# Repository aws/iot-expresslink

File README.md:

## AWS IoT ExpressLink

Watch [this overview presentation](https://www.youtube.com/watch?v=6K9knXZpC8A) to get a better understanding of what AWS IoT ExpressLink provides.

This repository contains examples for integrating an AWS IoT ExpressLink module into an application.  These examples are intended to demonstrate how to perform the common operations for an IoT device.

The AWS IoT ExpressLink AT command specification can be found in the [Programmer's Manual](https://docs.aws.amazon.com/iot-expresslink).

Information about AWS IoT ExpressLink and partner's hardware modules can be found at AWS Partner Network's Device Catalog from the [main page](https://aws.amazon.com/iot-expresslink). Module datasheet, Getting Started Guide, and Product Information are also included in the device catalog.

## Documentation

* [AWS IoT ExpressLink Programmer's Guide](https://docs.aws.amazon.com/iot-expresslink/latest/programmersguide/elpg.html)
* [AWS IoT ExpressLink Getting Started Guide](https://docs.aws.amazon.com/iot-expresslink/latest/gettingstartedguide/elgsg.html)
* [AWS IoT ExpressLink Onboarding-by-Claim Customer/OEM Guide](https://docs.aws.amazon.com/iot-expresslink/latest/oemonboardingguide/oemog.html)

## Prototyping SDK libraries
### C libraries
ExpressLink drivers and examples written in C for different MCU platforms.
#### STM32
CMSIS pack for ExpressLink driver and examples, integrated with STM32CubeMX, the native configuration and code generation tool from STMicroelectronics.
The combination enables developers to quickly and easily create applications that connect to AWS IoT Core using ExpressLink modules with various STM32 MCUs.
https://github.com/stm32-hotspot/I-CUBE-ExpressLink

### Python, CircuitPython, MicroPython

For Python, including CircuitPython, MicroPython, and standard Python on Linux, macOS, and Windows:
https://github.com/awslabs/aws-iot-expresslink-library-python

### Arduino

For Arduino and all all microcontrollers that support the Arduino platform:
https://github.com/awslabs/aws-iot-expresslink-library-arduino

## Web Resources

* [AWS IoT ExpressLink product page](https://aws.amazon.com/iot-expresslink/?nc=sn&loc=1)
* [AWS Partner Device Catalog for qualified AWS IoT ExpressLink hardware](https://devices.amazonaws.com/search?page=1&sv=iotxplnk)

## User Guides

The user guides can be found under the folder [cloud_templates/user_guides](cloud_templates/user_guides).

### Espressif

[Getting Started Guide for Espressif's AWS IoT ExpressLink Evaluation Kit on GitHub](https://github.com/espressif/esp-aws-expresslink-eval)

### Realtek

[Realtek's Ameba Z2 AWS IoT ExpressLink Evaluation Kit on GitHub](https://github.com/ambiot/ambz2_aws_iot_expresslink_eval)

### u-blox

[u-blox' USB-NORA-W256AWS AWS IoT ExpressLink Multiradio development kit](https://www.u-blox.com/en/product/usb-nora-w2?legacy=Current#Documentation-&-resources)

[u-blox' SARA-R510AWS module LTE-M AWS IoT ExpressLink module](https://www.u-blox.com/en/product/sara-r510aws-module?legacy=Current#Documentation-&-resources)

### Telit

[Telit's Bravo AWS IoT ExpressLink development kit on GitHub](https://github.com/telit/bravo-aws-expresslink)

## Hands-On Workshops and Resources

The **AWS IoT ExpressLink Demo Badge Workshop** is available at https://catalog.workshops.aws/aws-iot-expresslink-demo-badge/. This workshop ran as *IOT207-R* on November 28, and as *IOT207-R1* on December 2, at AWS re:Invent 2022.

The *Advanced Lab Modules* of the AWS re:Invent 2022 workshop used a Python library to quickly prototype an integration with AWS IoT ExpressLink using Python. The evolution of this early library is now available in this GitHub repository:
[awslabs/aws-iot-expresslink-library-python](https://github.com/awslabs/aws-iot-expresslink-library-python)

## Hardware Designs

The **AWS IoT ExpressLink Demo Badge hardware design**, with full schematics and PCB layout files, is available under the [hardware designs folder](./hardware-designs/).

## Blog Posts and Application Notes

* [Introducing AWS IoT ExpressLink, making it faster and easier to develop secure IoT devices](https://aws.amazon.com/blogs/iot/introducing-aws-iot-expresslink-making-it-faster-and-easier-to-develop-secure-iot-devices/) published 2021-11-30.
* [AWS IoT ExpressLink is now generally available](https://aws.amazon.com/about-aws/whats-new/2022/06/aws-iot-expresslink-generally-available/) published 2022-06-22.

## Twitch series: All Things AWS IoT ExpressLink

* Live stream on AWS Twitch channel - https://twitch.tv/aws
* Aired Tuesdays, 8am - 9am Pacific
* 15 episodes from March 15 - June 21, 2022
* Hosted by Dan Gross

 Episode    | Date       | Link                                       | Guest(s)                         | Partner  |
 ---------- | ---------- | ------------------------------------------ | -------------------------------- | -------- |
 Episode 1  | 2022-03-15 | https://www.twitch.tv/aws/video/1486749698 | Lucio, Michael                   |          |
 Episode 2  | 2022-03-22 | https://www.twitch.tv/aws/video/1486743174 | Lucio                            |          |
 Episdoe 3  | 2022-03-29 | https://www.twitch.tv/aws/video/1308163094 | Lucio, Magnus, Harald            | u-blox   |
 Episode 4  | 2022-04-05 | https://www.twitch.tv/aws/video/1314933253 | Lucio, Cobus, Joe                |          |
 Episode 5  | 2022-04-12 | https://www.twitch.tv/aws/video/1499049648 | Lucio, Harald, Magnus, Leo       | u-blox   |
 Episode 6  | 2022-04-19 | https://www.twitch.tv/aws/video/1507258985 | Cobus, Richard, Michael          |          |
 Episode 7  | 2022-04-26 | https://www.twitch.tv/aws/video/1507261412 | Lucio, Anton, Amey               | Espressif|
 Episode 8  | 2022-05-03 | https://www.twitch.tv/aws/video/1507263672 | Lucio, Joe                       |          |
 Episode 9  | 2022-05-10 | https://www.twitch.tv/aws/video/1507266090 | Lucio, Amey, Dhaval              | Espressif|
 Episode 10 | 2022-05-17 | https://www.twitch.tv/aws/video/1507267356 | Lucio, Yasser                    |          |
 Episode 11 | 2022-05-24 | https://www.twitch.tv/aws/video/1532014170 | Lucio, Amit, Prejith             | Infineon |
 Episode 12 | 2022-05-31 | https://www.twitch.tv/aws/video/1532015120 | Lucio, Joe                       |          |
 Episode 13 | 2022-06-07 | https://www.twitch.tv/aws/video/1532015794 | Lucio, Amit                      | Infineon |
 Episode 14 | 2022-06-14 | https://www.twitch.tv/aws/video/1532016601 | Lucio, Mike                      |          |
 Episode 15 | 2022-06-21 | https://www.twitch.tv/aws/video/1532017442 | Lucio, Steve, Magnus, Amey, Dave | All      |
 Episode 16 | 2022-11-22 | https://www.twitch.tv/aws/video/1690204748 | Lucio, Jefferson, Elleson, Shimis| Realtek |

## YouTube Videos

* [Playlist: Building a Weather Station](https://www.youtube.com/watch?v=hGBIzlp68bU&list=PLhr1KZpdzukdy_S7NpE9kkC75SXUCMYdO)
* [Espressif's AWS IoT ExpressLink Solution](https://www.youtube.com/watch?v=NSGCVH0OU7w)
* [u-blox AWS IoT ExpressLink](https://www.youtube.com/watch?v=4GiBnT0I0HE)
* [AWS IoT ExpressLink and the u-blox NORA-W2](https://www.youtube.com/watch?v=PvyzQwVgCCw)
* [Product Showcase: AWS IoT ExpressLink SARA-R5 Starter Kit](https://www.youtube.com/watch?v=nJNYUP0413c)
* [AIROC™ Cloud Connectivity Manager module & AWS IoT ExpressLink](https://www.youtube.com/watch?v=LEGDyNXPYfc)
* [Innovation Coffee with AWS IoT ExpressLink](https://www.youtube.com/watch?v=K0saFj-6s6c)
* [Connecting AWS IoT ExpressLink to an MQTT Broker running on AWS IoT Greengrass](https://www.youtube.com/watch?v=ii59MiFVIDI)

## Security

See [CONTRIBUTING](CONTRIBUTING.md#security-issue-notifications) for more information.

## License

The resources in this repository are licensed under the MIT-0 License. See the LICENSE file.

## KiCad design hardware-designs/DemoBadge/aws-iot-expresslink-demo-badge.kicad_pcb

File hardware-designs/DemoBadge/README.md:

# AWS IoT ExpressLink Demo Badge

This device was designed and created for the [AWS IoT ExpressLink Demo Badge Workshop](https://catalog.workshops.aws/aws-iot-expresslink-demo-badge/), which was run at re:Invent 2022.

The Demo Badge features an RP2040 microcontroller, an Espressif ESP32-C3-MINI-1-A AWS IoT ExpressLink module, various sensors, buttons, RGB LEDs, and a color display.

You can find more information about the device itself, and its components, as part of the [workshop appendix](https://catalog.workshops.aws/aws-iot-expresslink-demo-badge/en-US/7-appendix).

## Schematic

The schematic for the Demo Badge is available as KiCAD 6 project. You can access a [PDF version of the single-sheet schematic here](./snapshot/Schematic/aws-iot-expresslink-demo-badge-schematic.pdf).

## PCB Layout

The PCB layout for the Demo Badge is available as KiCAD 6 project, including all footprints (publicly available ones, and custom ones).

You can access the [production Gerber files here](./snapshot/Manufacturers/JLCPCB/).

## Re-generate Gerbers and other files

If you made any changes to the PCB layout, you have to re-generate the Gerbers files before sending them to your PCB manufacturer. You can use [KiBot](https://github.com/INTI-CMNB/KiBot) to generate Gerbers and other files in a repeatable way using the `kibot.yaml` configuration file.

You can follow the KiBot installation guide, or use a Docker container:

```bash
docker run --rm -v "$PWD":/kicad -w /kicad setsoft/kicad_auto:ki6 kibot -c kibot.yaml
```

All KiBot-generated files are available under `Generated/`.

## License

This hardware design is licensed under the MIT-0 License. Imported footprints and 3D models might contain different licenses.

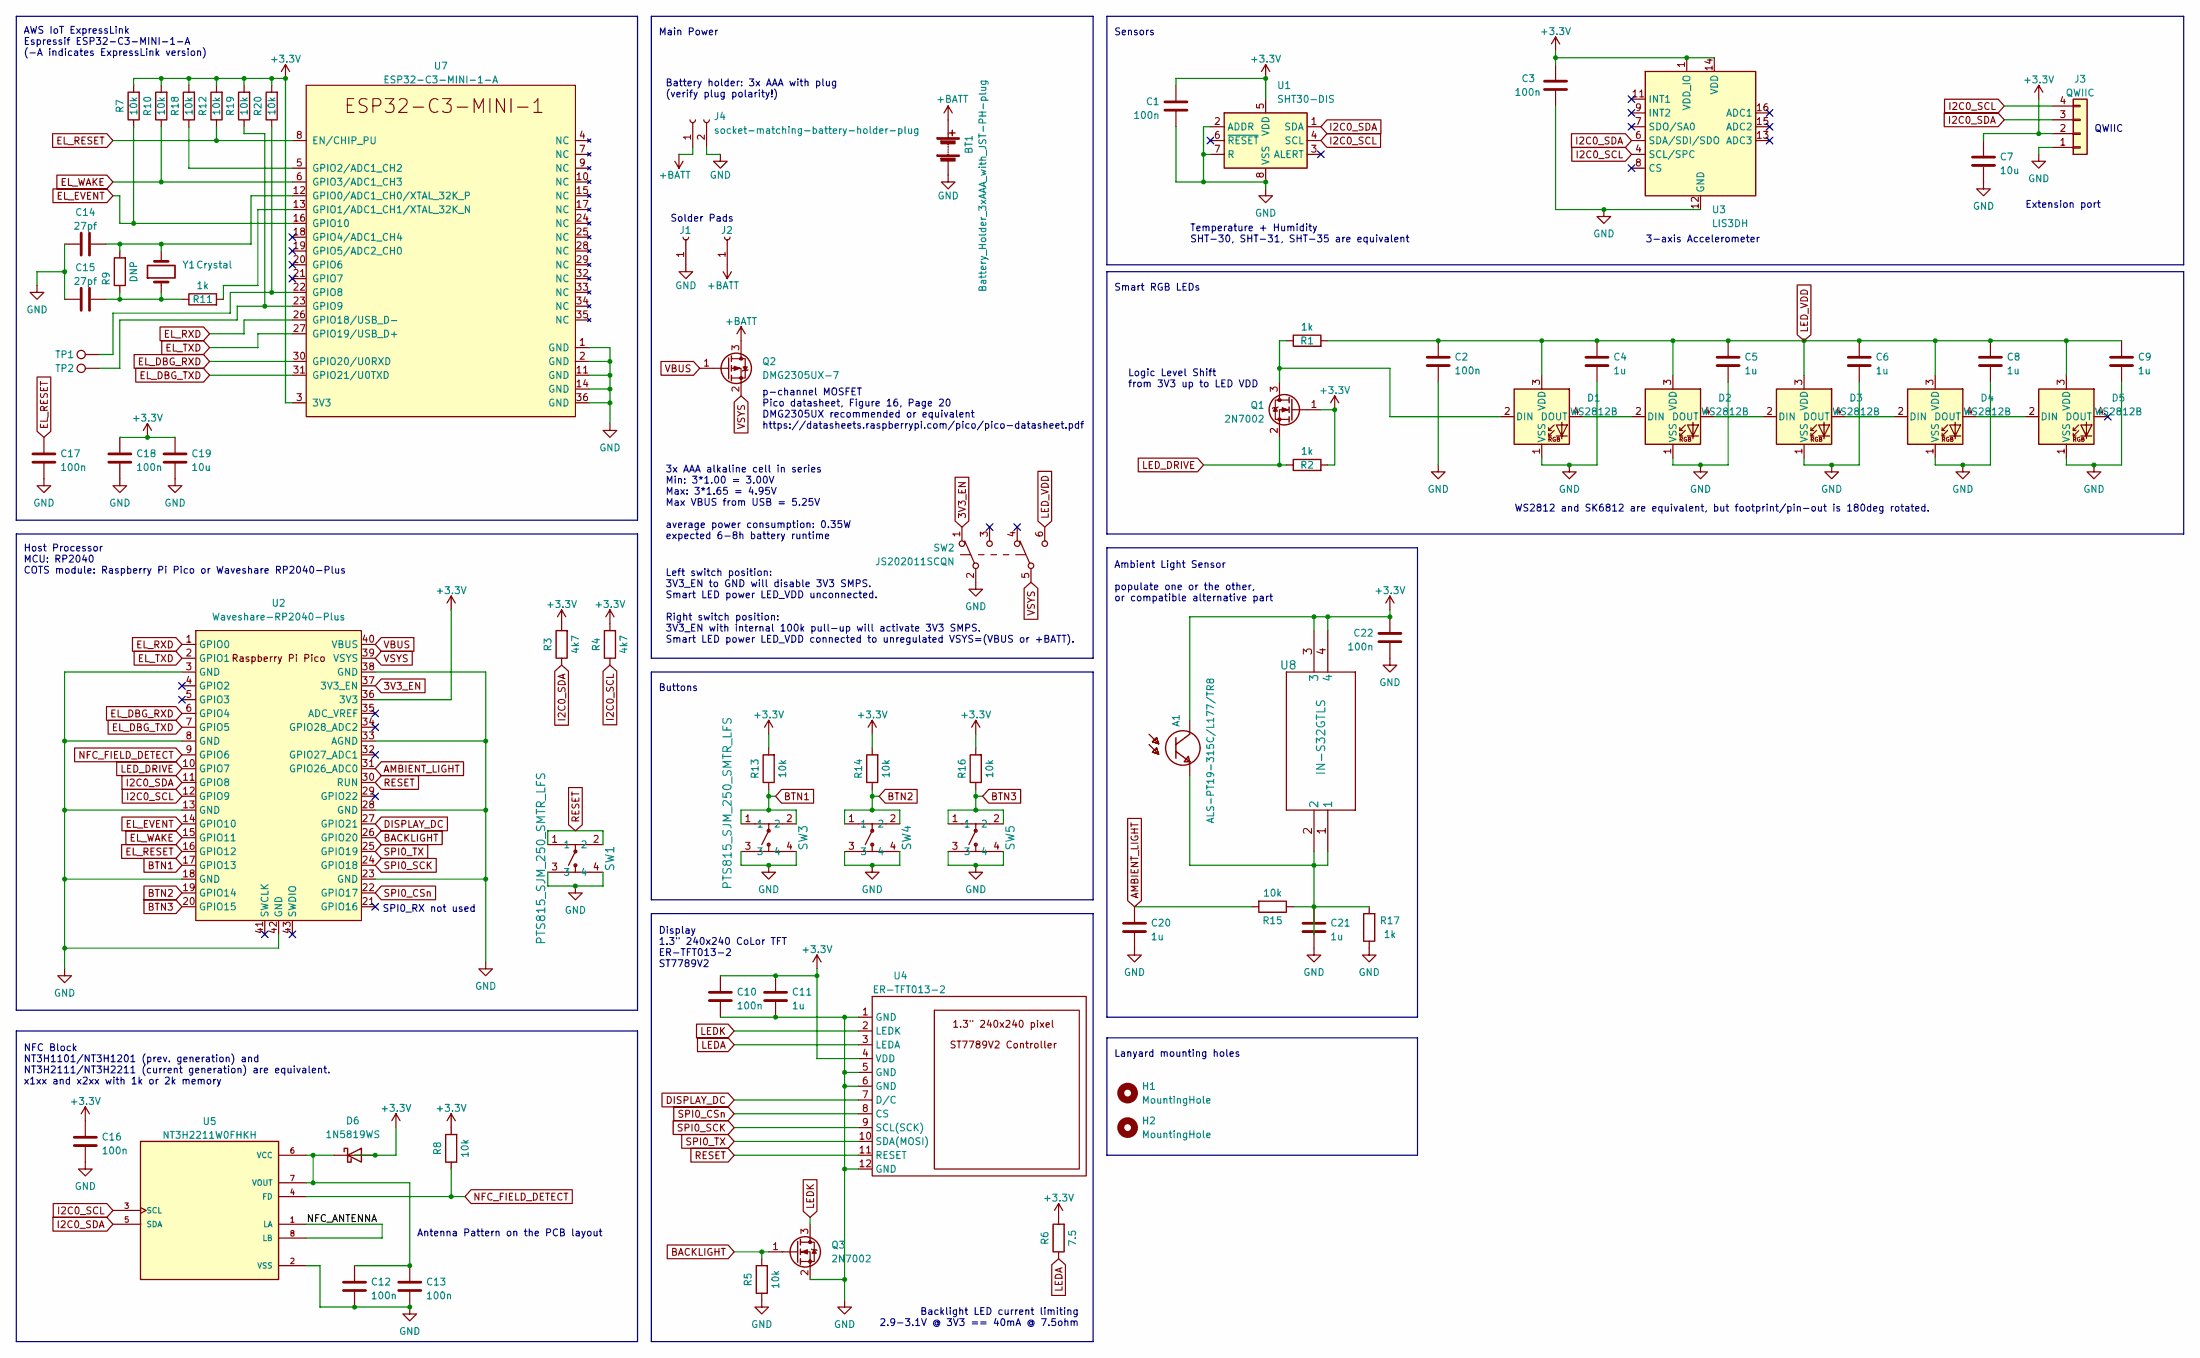
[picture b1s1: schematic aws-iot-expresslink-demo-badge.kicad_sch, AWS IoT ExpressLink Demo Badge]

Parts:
A1: ALS-PT19-315C/L177/TR8; XDCR_ALS-PT19-315C_L177_TR8; LCSC# C146233
BT1: Battery_Holder_3xAAA_with_JST-PH-plug
C1, C2, C3, C10, C12, C13, C16, C17, C18, C22: 100n; C_0603_1608Metric; LCSC# C14663
C4, C5, C6, C8, C9, C11, C20, C21: 1u; C_0603_1608Metric; LCSC# C15849
C7, C19: 10u; C_0603_1608Metric; LCSC# C19702
C14, C15: 27pf; C_0603_1608Metric; LCSC# C107045
D1, D2, D3, D4, D5: WS2812B; SK6812-multi; LCSC# C2874885
D6: 1N5819WS; D_SOD-323; LCSC# C191023
H1, H2: MountingHole; lanyard-cutout
J1: BATT_NEG; TestPoint_Pad_D2.0mm
J2: BATT_POS; TestPoint_Pad_D2.0mm
J3: QWIIC; JST_SH_SM04B-SRSS-TB_1x04-1MP_P1.00mm_Horizontal; LCSC# C145956
J4: socket-matching-battery-holder-plug; JST_PH_S2B-PH-K_1x02_P2.00mm_Horizontal; LCSC# C173752
Q1, Q3: 2N7002; SOT-23; LCSC# C8545
Q2: DMG2305UX-7; SOT-23; LCSC# C150470
R1, R2, R11, R17: 1k; R_0603_1608Metric; LCSC# C21190
R3, R4: 4k7; R_0603_1608Metric; LCSC# C105428
R5, R7, R8, R10, R12, R13, R14, R15, R16, R18, R19, R20: 10k; R_0603_1608Metric; LCSC# C25804
R6: 7.5; R_0603_1608Metric; LCSC# C365480
R9: DNP; R_0603_1608Metric
SW1, SW3, SW4, SW5: PTS815_SJM_250_SMTR_LFS; PTS815 SJM 250 SMTR LFS; LCSC# C2689510
SW2: JS202011SCQN; LCSC# C221666
TP1, TP2: TestPoint; TestPoint_Pad_D1.0mm
U1: SHT30-DIS; Sensirion_DFN-8-1EP_2.5x2.5mm_P0.5mm_EP1.1x1.7mm; LCSC# C77361
U2: Waveshare-RP2040-Plus; LCSC# C5159530
U3: LIS3DH; LGA-16_3x3mm_P0.5mm_LayoutBorder3x5y; LCSC# C15134
U4: ER-TFT013-2
U5: NT3H2211W0FHKH; IC_NT3H2211W0FHKH; LCSC# C2905792
U7: ESP32-C3-MINI-1-A; ESP32-C3-MINI-1; LCSC# C5224444
U8: IN-S32GTLS
Y1: Crystal; Crystal_SMD_3215-2Pin_3.2x1.5mm; LCSC# C32346

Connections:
3V3_EN: SW2.1 (A), U2.37 (3V3_EN)
+3.3V: A1.1, C1.2, C3.2, C7.2, C10.2, C11.2, C16.2, C18.2, C19.2, C22.2, D6.2 (A), J3.2, Q1.1 (G), R2.2, R3.2, R4.2, R6.2, R7.2, R8.2, R10.2, R12.2, R13.2, R14.2, R16.2, R18.2, R19.2, R20.2, U1.5 (VDD), U2.36 (3V3), U3.1 (VDD_IO), U3.14 (VDD), U4.4 (VDD), U7.3 (3V3), U8.3, U8.4
+BATT: BT1.1 (+), J2.1, J4.1, Q2.3 (D)
/NFC_ANTENNA: U5.1 (LA), U5.8 (LB)
AMBIENT_LIGHT: C20.2, R15.2, U2.31 (GPIO26_ADC0)
BACKLIGHT: Q3.1 (G), R5.2, U2.26 (GPIO20)
BTN1: R13.1, SW3.1, SW3.2, U2.17 (GPIO13)
BTN2: R14.1, SW4.1, SW4.2, U2.19 (GPIO14)
BTN3: R16.1, SW5.1, SW5.2, U2.20 (GPIO15)
DISPLAY_DC: U2.27 (GPIO21), U4.7 (D/C)
EL_DBG_RXD: U2.6 (GPIO4), U7.30 (GPIO20/U0RXD)
EL_DBG_TXD: U2.7 (GPIO5), U7.31 (GPIO21/U0TXD)
EL_EVENT: R7.1, U2.14 (GPIO10), U7.16 (GPIO10)
EL_RESET: C17.1, R12.1, U2.16 (GPIO12), U7.8 (EN/CHIP_PU)
EL_RXD: U2.1 (GPIO0), U7.26 (GPIO18/USB_D-)
EL_TXD: U2.2 (GPIO1), U7.27 (GPIO19/USB_D+)
EL_WAKE: R10.1, U2.15 (GPIO11), U7.6 (GPIO3/ADC1_CH3)
GND: BT1.2 (-), C1.1, C2.1, C3.1, C4.1, C5.1, C6.1, C7.1, C8.1, C9.1, C10.1, C11.1, C12.1, C13.1, C14.1, C15.1, C16.1, C17.2, C18.1, C19.1, C20.1, C21.1, C22.1, D1.1 (VSS), D2.1 (VSS), D3.1 (VSS), D4.1 (VSS), D5.1 (VSS), J1.1, J3.1, J4.2, Q3.2 (S), R5.1, R17.1, SW1.3, SW1.4, SW2.2 (B), SW3.3, SW3.4, SW4.3, SW4.4, SW5.3, SW5.4, U1.2 (ADDR), U1.7 (R), U1.8 (VSS), U1.9 (VSS), U2.3 (GND), U2.8 (GND), U2.13 (GND), U2.18 (GND), U2.23 (GND), U2.28 (GND), U2.33 (AGND), U2.38 (GND), U2.42 (GND), U3.5 (GND), U3.10 (GND), U3.12 (GND), U4.1 (GND), U4.5 (GND), U4.6 (GND), U4.12 (GND), U5.2 (VSS), U7.1 (GND), U7.2 (GND), U7.11 (GND), U7.14 (GND), U7.36 (GND)
I2C0_SCL: J3.4, R4.1, U1.4 (SCL), U2.12 (GPIO9), U3.4 (SCL/SPC), U5.3 (SCL)
I2C0_SDA: J3.3, R3.1, U1.1 (SDA), U2.11 (GPIO8), U3.6 (SDA/SDI/SDO), U5.5 (SDA)
LEDA: R6.1, U4.3 (LEDA)
LEDK: Q3.3 (D), U4.2 (LEDK)
LED_DRIVE: Q1.2 (S), R2.1, U2.10 (GPIO7)
LED_VDD: C2.2, C4.2, C5.2, C6.2, C8.2, C9.2, D1.3 (VDD), D2.3 (VDD), D3.3 (VDD), D4.3 (VDD), D5.3 (VDD), R1.2, SW2.6 (C)
NFC_FIELD_DETECT: R8.1, U2.9 (GPIO6), U5.4 (FD)
unnamed: A1.2, C21.2, R15.1, R17.2, U8.1, U8.2
unnamed: C12.2, C13.2, D6.1 (K), U5.6 (VCC), U5.7 (VOUT)
unnamed: C14.2, R9.2, U7.12 (GPIO0/ADC1_CH0/XTAL_32K_P), Y1.2
unnamed: C15.2, R9.1, R11.1, Y1.1
unnamed: D1.2 (DIN), Q1.3 (D), R1.1
unnamed: D1.4 (DOUT), D2.2 (DIN)
unnamed: D2.4 (DOUT), D3.2 (DIN)
unnamed: D3.4 (DOUT), D4.2 (DIN)
unnamed: D4.4 (DOUT), D5.2 (DIN)
unnamed: R11.2, U7.13 (GPIO1/ADC1_CH1/XTAL_32K_N)
unnamed: R18.1, U7.5 (GPIO2/ADC1_CH2)
unnamed: R19.1, TP2.1, U7.23 (GPIO9)
unnamed: R20.1, TP1.1, U7.22 (GPIO8)
RESET: SW1.1, SW1.2, U2.30 (RUN), U4.11 (RESET)
SPI0_CSn: U2.22 (GPIO17), U4.8 (CS)
SPI0_SCK: U2.24 (GPIO18), U4.9 (SCL(SCK))
SPI0_TX: U2.25 (GPIO19), U4.10 (SDA(MOSI))
VBUS: Q2.1 (G), U2.40 (VBUS)
VSYS: Q2.2 (S), SW2.5 (B), U2.39 (VSYS)

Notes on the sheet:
Solder Pads
Main Power
Sensors
Host Processor MCU: RP2040 COTS module: Raspberry Pi Pico or Waveshare RP2040-Plus
AWS IoT ExpressLink Espressif ESP32-C3-MINI-1-A (-A indicates ExpressLink version)
Left switch position: 3V3_EN to GND will disable 3V3 SMPS. Smart LED power LED_VDD unconnected. Right switch position: 3V3_EN with internal 100k pull-up will activate 3V3 SMPS. Smart LED power LED_VDD connected to unregulated VSYS=(VBUS or +BATT).
NFC Block NT3H1101/NT3H1201 (prev. generation) and NT3H2111/NT3H2211 (current generation) are equivalent. x1xx and x2xx with 1k or 2k memory
SPI0_RX not used
3-axis Accelerometer
Smart RGB LEDs
Battery holder: 3x AAA with plug (verify plug polarity!)
Display 1.3" 240x240 CoLor TFT ER-TFT013-2 ST7789V2
Logic Level Shift from 3V3 up to LED VDD
3x AAA alkaline cell in series Min: 3*1.00 = 3.00V Max: 3*1.65 = 4.95V Max VBUS from USB = 5.25V average power consumption: 0.35W expected 6-8h battery runtime
p-channel MOSFET Pico datasheet, Figure 16, Page 20 DMG2305UX recommended or equivalent https://datasheets.raspberrypi.com/pico/pico-datasheet.pdf
Temperature + Humidity SHT-30, SHT-31, SHT-35 are equivalent
QWIIC
Lanyard mounting holes
Extension port
Antenna Pattern on the PCB layout
Ambient Light Sensor populate one or the other, or compatible alternative part
WS2812 and SK6812 are equivalent, but footprint/pin-out is 180deg rotated.
Buttons
Backlight LED current limiting 2.9-3.1V @ 3V3 == 40mA @ 7.5ohm

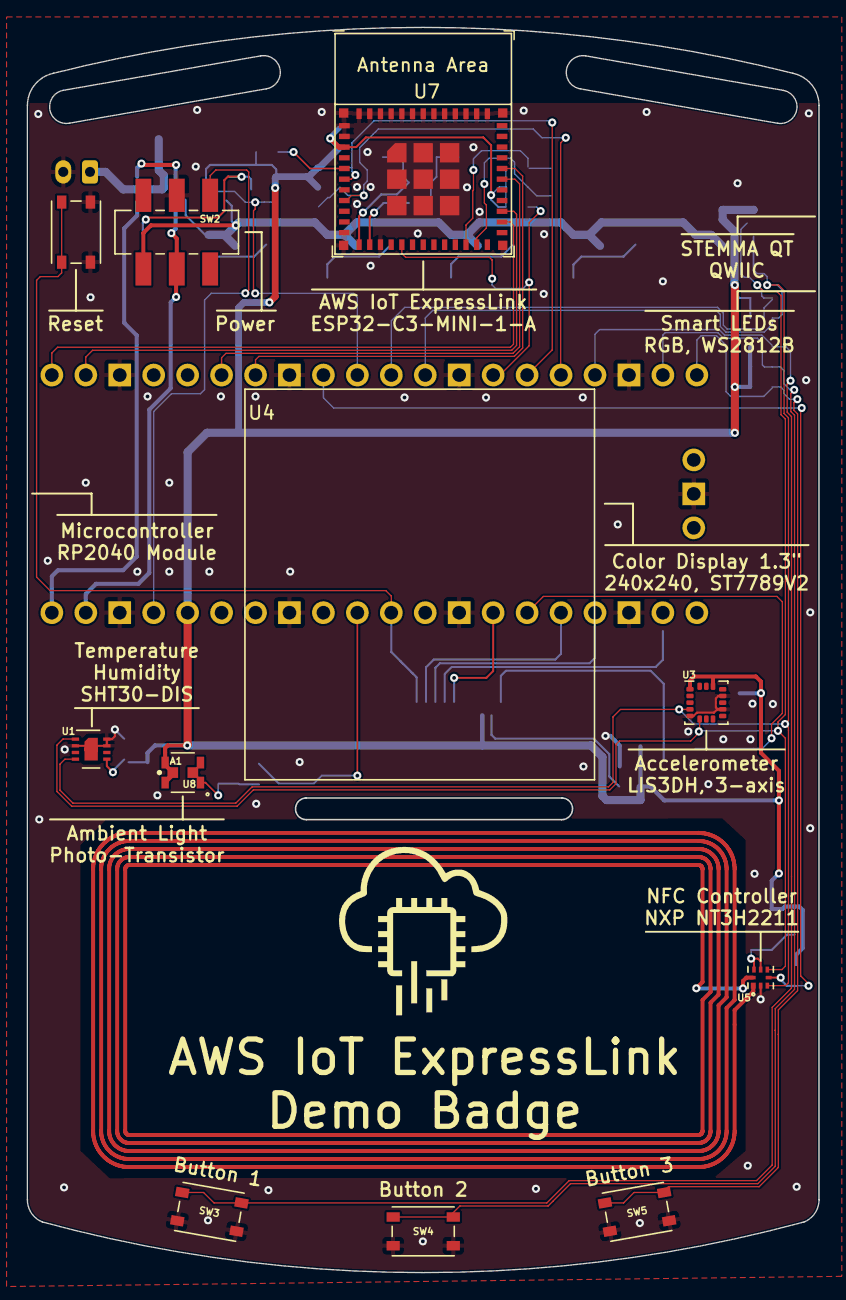
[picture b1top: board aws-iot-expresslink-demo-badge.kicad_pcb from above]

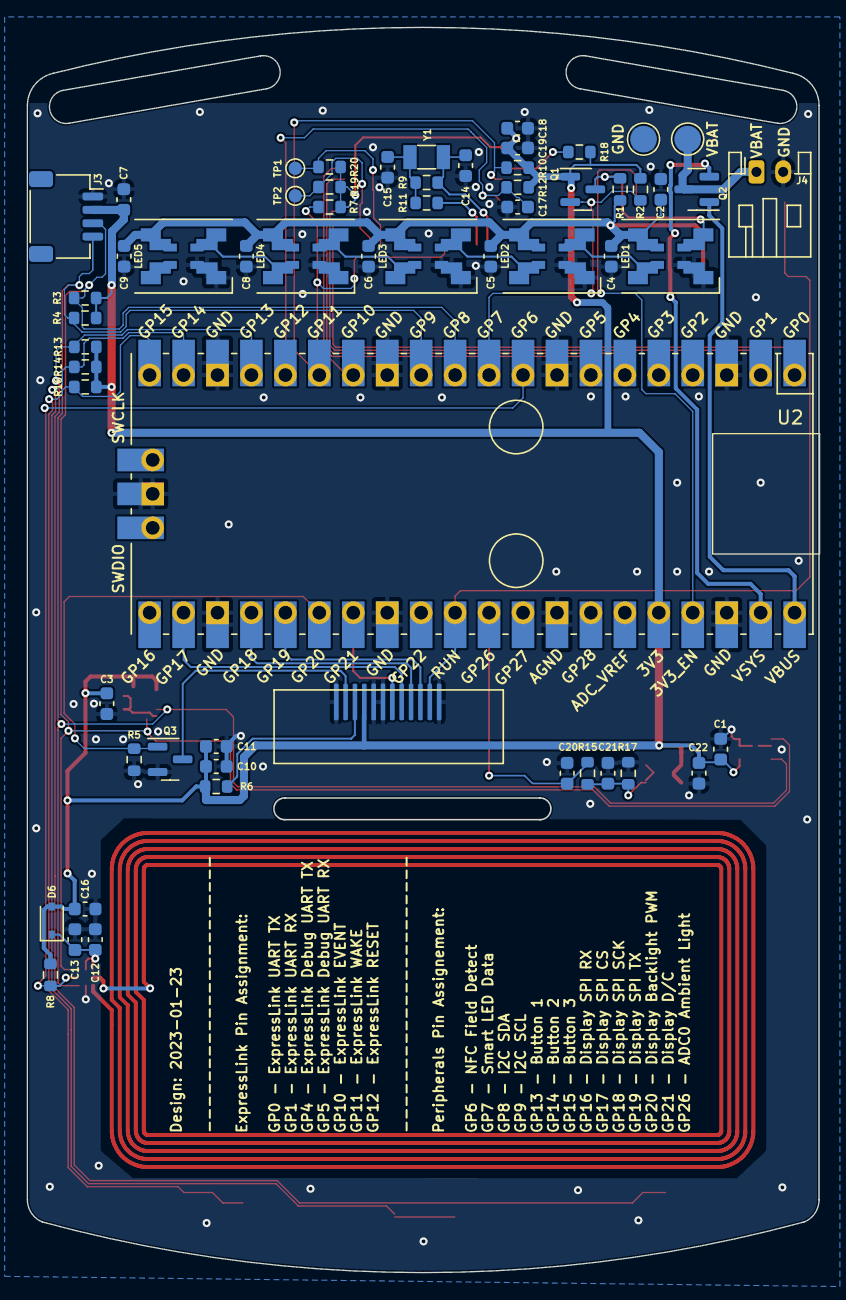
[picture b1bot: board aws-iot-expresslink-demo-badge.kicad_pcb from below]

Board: 2 copper layers, 59.2 x 93.2 mm, 73 parts (59 on the bottom side), 44 nets.

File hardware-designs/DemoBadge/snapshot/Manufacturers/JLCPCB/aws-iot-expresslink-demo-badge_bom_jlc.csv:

"Comment","Designator","Footprint","LCSC Part #"
"ALS-PT19-315C/L177/TR8","A1","XDCR_ALS-PT19-315C_L177_TR8","C146233"
"27pf","C14,C15","C_0603_1608Metric","C107045"
"100n","C1,C2,C3,C10,C12,C13,C16,C17,C18,C22","C_0603_1608Metric","C14663"
"1u","C4,C5,C6,C8,C9,C11,C20,C21","C_0603_1608Metric","C15849"
"10u","C7,C19","C_0603_1608Metric","C19702"
"1N5819WS","D6","D_SOD-323","C191023"
"WS2812B","D1,D2,D3,D4,D5","SK6812-multi","C2874885"
"QWIIC","J3","JST_SH_SM04B-SRSS-TB_1x04-1MP_P1.00mm_Horizontal","C145956"
"socket-matching-battery-holder-plug","J4","JST_PH_S2B-PH-K_1x02_P2.00mm_Horizontal","C173752"
"2N7002","Q1,Q3","SOT-23","C8545"
"DMG2305UX-7","Q2","SOT-23","C150470"
"7.5","R6","R_0603_1608Metric","C365480"
"1k","R1,R2,R11,R17","R_0603_1608Metric","C21190"
"4k7","R3,R4","R_0603_1608Metric","C105428"
"10k","R5,R7,R8,R10,R12,R13,R14,R15,R16,R18,R19,R20","R_0603_1608Metric","C25804"
"JS202011SCQN","SW2","JS202011SCQN","C221666"
"PTS815_SJM_250_SMTR_LFS","SW1,SW3,SW4,SW5","PTS815 SJM 250 SMTR LFS","C2689510"
"ESP32-C3-MINI-1-A","U7","ESP32-C3-MINI-1","C5224444"
"LIS3DH","U3","LGA-16_3x3mm_P0.5mm_LayoutBorder3x5y","C15134"
"NT3H2211W0FHKH","U5","IC_NT3H2211W0FHKH","C2905792"
"SHT30-DIS","U1","Sensirion_DFN-8-1EP_2.5x2.5mm_P0.5mm_EP1.1x1.7mm","C77361"
"Waveshare-RP2040-Plus","U2","Waveshare-RP2040-Plus","C5159530"
"Crystal","Y1","Crystal_SMD_3215-2Pin_3.2x1.5mm","C32346"

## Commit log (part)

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2021-11-19 Initial checkin of first projects
2021-11-19 simplified code
2021-11-30 Create CODEOWNERS
2021-11-30 Add PULL_REQUEST_TEMPLATE
2021-12-23 Update README.md
    Add link to RedBoard Turbo Fun set up instruction.
2022-04-01 removed TopicRoot set... this should be pre-provisioned
2022-04-01 Added grafana demo to arduino examples
2022-04-04 Tweaks to the data report
2022-04-29 First working version of the Cellular ExpressLink WeatherStation
2022-04-29 Removed the topicroot from the prefix of the data topic
2022-05-03 Updated the reconnection strategy
2022-05-09 Adding Arduino Uno example for weather station project
2022-08-16 Added the AWS CDK code for the patterns - first version
2022-08-24 Deletes the massive directory
2022-08-24 Added Timestream pattern material
2022-08-24 Updated the top-level README
2022-08-24 Added the demo main.cpp file and its instructions
2022-08-24 Added the IoT Analytics pattern material
2022-08-25 Seperated Timestream branch from main
2022-08-25 Added the common directory - common files and functions between all the patterns
2022-08-25 Added the common directory - common files and functions for all the patterns
2022-08-25 Fixed the common directory commit
2022-08-25 Added gitignore to IoT Analytics branch
2022-08-25 Added the content for OpenSearch Pattern CDK Template
2022-08-25 Fixed the typo in README.md
2022-08-25 Added the Kinesis Pattern CDK Template
2022-08-25 Fixed a few typos in Timestream user guide
2022-08-25 Added the cdk stack structure images for user guides
2022-08-25 Added the structure image to Timestream user guide
2022-08-25 Updated the iotanalytics user guide fixed typos
2022-08-25 Fixed typos and added structure image to userguide
2022-08-25 Added the structure img + fixed typos in userguide
2022-08-26 Added the new kinesis branch - no conflict with timestream
2022-08-26 Added the new iot analytics branch - no conflict with timestream
2022-08-26 Added the new opensearch branch - no conflict with timestream
2022-09-07 Fixed the OpenSearch Document type / missing image
    The OpenSearch CDK application's structure image was missed in the previous version of the guide. This commit fixed that typo.
2022-09-09 Updated toplevel README with patterns' description
2022-11-18 Updates Readme with user guide location
2022-11-18 Updates Readme to support relative link
2023-02-10 add hardware design: AWS IoT ExpressLink Demo Badge
2023-02-13 readme: add more resources and link collection
2023-02-20 Update README.md
    Add ExpressLink v1.1 and Real-tek module twitch episode.
2023-02-20 Update README.md
    Correct partner name typo
2023-03-12 add new prototyping libraries
2023-04-04 Add default S3 Managed encryption
    Adds default S3 managed encryption (using AES256)
    to the kensis json and CDK files. Corrects cdk command
    in user guide.
2023-04-06 Encrypt with KMS Customer Managed Key
    Using a CMK for bucket server side encryption
    is the recommended method for encryption.
2023-04-18 add new resources
2023-04-18 fix typo in session id
2023-06-22 Add I-CUBE-Expresslink to ReadMe
    Add SDK for C, and link to I-CUBE-ExpressLink from STMicroelectronics.
2023-06-22 Add C libraries section and link to STM32 package
    Add C libraries section and link to STM32 package
2023-06-22 Add C folder and README
2026-04-13 Bump pytest in /cloud_templates/aws_cdk/TimestreamPattern
    Bumps [pytest](https://github.com/pytest-dev/pytest) from 6.2.5 to 9.0.3.
    - [Release notes](https://github.com/pytest-dev/pytest/releases)
    - [Changelog](https://github.com/pytest-dev/pytest/blob/main/CHANGELOG.rst)
    - [Commits](https://github.com/pytest-dev/pytest/compare/6.2.5...9.0.3)
    ---
    updated-dependencies:
2026-04-21 Bump pytest in /cloud_templates/aws_cdk/IoTAnalyticsPattern
    Bumps [pytest](https://github.com/pytest-dev/pytest) from 6.2.5 to 9.0.3.
    - [Release notes](https://github.com/pytest-dev/pytest/releases)
    - [Changelog](https://github.com/pytest-dev/pytest/blob/main/CHANGELOG.rst)
    - [Commits](https://github.com/pytest-dev/pytest/compare/6.2.5...9.0.3)
    ---
    updated-dependencies:
2026-04-22 Update Pytest to 9.0.3
    pytest through 9.0.2 on UNIX relies on directories with the /tmp/pytest-of-{user} name pattern, which allows local users to cause a denial of service or possibly gain privileges.
    This resolves:
    * https://github.com/aws/iot-expresslink/security/dependabot/2
    * https://github.com/aws/iot-expresslink/security/dependabot/4

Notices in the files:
parts and their libraries:
Copyright 2021 Accelerated Designs. All rights reserved.
